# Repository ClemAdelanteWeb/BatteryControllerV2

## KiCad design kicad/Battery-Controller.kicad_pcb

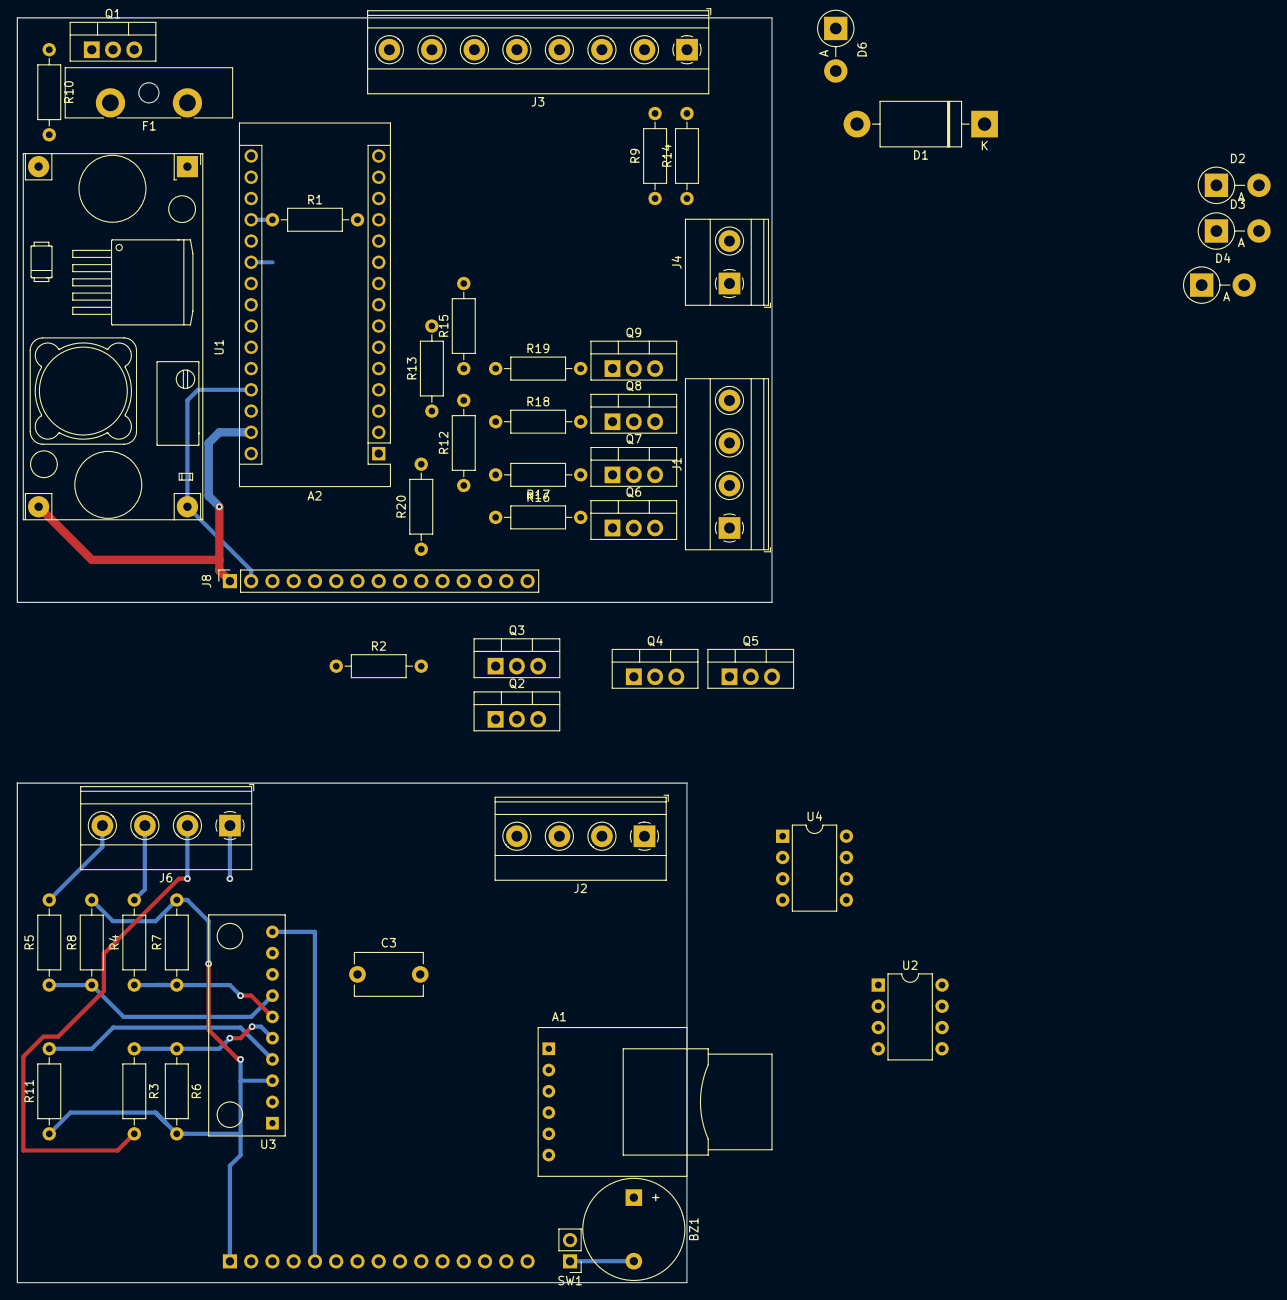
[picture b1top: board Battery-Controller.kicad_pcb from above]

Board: 2 copper layers, 90.2 x 151.1 mm, 51 parts (1 on the bottom side), 64 nets.

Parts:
A1: SD_Card_Module
A2: Arduino_Nano_v3.x; Arduino_Nano
BZ1: Buzzer; Buzzer_12x9.5RM7.6
C3: 0.1uF; C_Disc_D8.0mm_W5.0mm_P7.50mm
D1: 1N5822; D_DO-201AD_P15.24mm_Horizontal
D2, D3, D4, D6: 1N5822; D_5W_P5.08mm_Vertical_AnodeUp
F1: Fuse; Fuseholder_Blade_ATO_Littelfuse_Pudenz_2_Pin
J1: Screw_Terminal_01x04 - RELAY; TerminalBlock_Phoenix_MKDS-1,5-4-5.08_1x04_P5.08mm_Horizont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
J2: Screw_Terminal_01x04 - COM; TerminalBlock_Phoenix_MKDS-1,5-4-5.08_1x04_P5.08mm_Horizont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
J3: Screw_Terminal_01x08; TerminalBlock_Phoenix_MKDS-1,5-8-5.08_1x08_P5.08mm_Horizont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
J4: Screw_Terminal_01x02 - Battery IN; TerminalBlock_Phoenix_MKDS-1,5-2-5.08_1x02_P5.08mm_Horizont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
J6: Screw_Terminal_01x04 - Cells; TerminalBlock_Phoenix_MKDS-1,5-4-5.08_1x04_P5.08mm_Horizont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
J7: Conn_01x15_Male; PinHeader_1x15_P2.54mm_Vertical
J8: Conn_01x15_Female; PinSocket_1x15_P2.54mm_Vertical
Q1: TIP120; TO-220-3_Vertical
Q2, Q3, Q4, Q5: TIP122; TO-220-3_Vertical
Q6, Q7, Q8, Q9: TIP42C; TO-220-3_Vertical
R1, R9, R11, R14: 10K; R_Axial_DIN0207_L6.3mm_D2.5mm_P10.16mm_Horizontal
R2: 4.7K; R_Axial_DIN0207_L6.3mm_D2.5mm_P10.16mm_Horizontal
R3: 21.6K; R_Axial_DIN0207_L6.3mm_D2.5mm_P10.16mm_Horizontal
R4: 474; R_Axial_DIN0207_L6.3mm_D2.5mm_P10.16mm_Horizontal
R5: 5.1K; R_Axial_DIN0207_L6.3mm_D2.5mm_P10.16mm_Horizontal
R6: 32K; R_Axial_DIN0207_L6.3mm_D2.5mm_P10.16mm_Horizontal
R7: 330; R_Axial_DIN0207_L6.3mm_D2.5mm_P10.16mm_Horizontal
R8: 2.2K; R_Axial_DIN0207_L6.3mm_D2.5mm_P10.16mm_Horizontal
R10, R12, R13, R15, R16, R17, R18, R19, R20: 1K; R_Axial_DIN0207_L6.3mm_D2.5mm_P10.16mm_Horizontal
SW1: SW_DPST_x2; PinHeader_1x02_P2.54mm_Vertical
U1: YAAJ_DCDC_StepDown_LM2596
U2: DS1307+; DIP-8_W7.62mm
U3: ADS1115IDGS; ADC1115_ADC_Module
U4: SN75176AP; DIP-8_W7.62mm

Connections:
3.3V: A2.17, J8.3, R1.2
5V: A2.27, J3.6, J8.2, R9.1, R14.1, U1.4
A0: A2.19, J3.4, R1.1
A1: A2.20, R20.2
A2: A2.21, R12.2
A3: A2.22, J3.7, R2.1
A6: A2.25, J3.1, R14.2
A7: A2.26, J3.2, R9.2
BAT-12V: D2.2, D3.2, D4.2, D6.2, F1.1, J4.1, Q6.2, Q7.2, Q8.2, Q9.2, R16.1, R17.1, R18.1, R19.1
BAT-GND: A2.29, J3.3, J4.2, J8.1, Q2.3, Q3.3, Q4.3, Q5.3, R2.2, U1.2, U1.3
CELL-1: J6.1, R11.2, U3.4
CELL-2: J6.2, R3.2
CELL-3: J6.3, R4.2
CELL-4: J6.4, R5.2
CHARGE-RELAY-OFF: D2.1, J1.2, Q7.3
CHARGE-RELAY-ON: D6.1, J1.1, Q6.3
CHARGING-STATUS: J3.5, Q1.3
D2: A2.5, J8.10
D3: A2.6, J8.11
D4: A2.7, R13.2
D5: A2.8, R15.2
D6: A2.9, R10.2
D7: A2.10, J8.12
D8: A2.11, J8.13
D9: A2.12, J8.14
D10: A2.13, J8.7
D11: A2.14, J8.9
D12: A2.15, J8.8
D13: A2.16, J8.6
LOAD-RELAY-OFF: D4.1, J1.4, Q9.3
LOAD-RELAY-ON: D3.1, J1.3, Q8.3
unnamed: BZ1.2, SW1.1
unnamed: D1.1, U1.1
unnamed: F1.2, Q1.2
unnamed: Q1.1, R10.1
unnamed: Q2.1, R20.1
unnamed: Q2.2, Q6.1, R16.2
unnamed: Q3.1, R12.1
unnamed: Q3.2, Q7.1, R17.2
unnamed: Q4.1, R13.1
unnamed: Q4.2, Q8.1, R18.2
unnamed: Q5.1, R15.1
unnamed: Q5.2, Q9.1, R19.2
unnamed: R3.1, R6.1, U3.5
unnamed: R4.1, R7.1, U3.6
unnamed: R5.1, R8.1, U3.7
RS-485-OUT1: J2.3, U4.7
RS-485-OUT2: J2.4, U4.6
SCL: A2.24, J8.5
SDA: A2.23, J8.4
TUP-01: A1.6, BZ1.1, C3.2, J7.1, R6.2, R7.2, R8.2, R11.1, U2.4, U3.3, U4.5
UP-3.3V: A1.1, J7.3
UP-5V: C3.1, J7.2, U2.3, U3.8, U4.8
UP-CLK: A1.4, J7.6
UP-CS: A1.2, J7.7
UP-D2: J7.10, U4.4
UP-D3: J7.11, U4.1
UP-D7: J7.12, SW1.2
UP-MISO: A1.5, J7.8
UP-MOSI: A1.3, J7.9
UP-SCL: J7.5, U2.6, U3.10
UP-SDA: J7.4, U2.5, U3.9
VICTRON-IN-1: J2.1, J7.13
VICTRON-IN-2: J2.2, J7.14

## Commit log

2021-11-25 Fin schematic
2021-11-25 Mise à jour empreintes
2021-11-25 Mise en place composants
2021-12-01 Ajout logs SD Card
2021-12-02 Calibration entrées Cells
2021-12-02 Intégration des routines de surveillance de la température
2021-12-03 ne fonctionne pas ... pb serial connexion
2021-12-04 Print status, print params
2021-12-08 Optimisation du code
2021-12-12 Adding tests files
2021-12-14 Migration vers VS Code et PlatformIO
2021-12-14 Réécriture des codes d'erreur
2021-12-14 Mise en place carte SD
2021-12-14 optimisation pour sd card
2021-12-17 Mise en production
2021-12-18 Fonctionne, correctement réglé, NO serial transfer
2021-12-19 RS484 included, not enough ram
2021-12-19 New RTC validé
2021-12-19 Utilisation de SdFat library
2021-12-19 Optimisation
2021-12-20 Fonctionne, avant checksum validation
2021-12-20 Fonctionne en RS485 Sans RTC
2021-12-20 Retrait de la verification des différences de cellules
2021-12-24 Bugfix highest cell voltage and lowest cell voltage
2021-12-26 Bugfixes
2021-12-26 Readme
2021-12-27 Mise à jour ADS1115 gain et calibration
2021-12-29 Checksum
2021-12-29 RS485 free memory
2021-12-30 Print Params
2022-01-01 petites corrections
